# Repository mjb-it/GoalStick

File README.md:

# GoalStick

An NHL goal celebration system that triggers LED light shows when your favorite team scores. The system consists of three components:

- **Raspberry Pi Service** (Python) - Monitors NHL games and detects goals
- **Android App** (Kotlin) - Companion app for configuration via Bluetooth
- **ESP32 Firmware** (Arduino/C++) - Controls WS2812B LED strip animations

## Repository Structure

```
GoalStick/
├── PythonSrc/       # Raspberry Pi Python service
├── Android/         # Android companion app
├── ESP32/           # ESP32 LED controller firmware
├── Makefile         # Build and test automation
└── README.md
```

---

# Raspberry Pi Service (Python)

The core service that monitors NHL games and communicates with the ESP32 to trigger celebrations.

## Requirements

- Raspberry Pi Zero 2 W (or any Pi with GPIO)
- Python 3.9+
- Serial connection to ESP32

## Installation

```bash
cd PythonSrc
pip install -e .
```

Or using Make:
```bash
make python-install
```

## Usage

```bash
cd PythonSrc

# Start the goal monitoring service
python main.py

# Set your team (persists across reboots)
python main.py --team WSH

# Show currently configured team
python main.py --show-team

# Enter Bluetooth pairing mode
python main.py --pair
```

## Testing

```bash
# Run unit tests (69 tests)
make python-test

# Run with coverage report
make python-test-cov
```

## Configuration Options

| Parameter | Type | Default | Description |
|-----------|------|---------|-------------|
| `team_abbr` | str | "WSH" | NHL team abbreviation |
| `check_interval` | float | 2.0 | Seconds between goal checks during live games |
| `daily_check_hour` | int | 8 | Hour (24-hour format) to check daily schedule |
| `pre_game_wake_minutes` | int | 5 | Minutes before game to wake up |
| `serial_port` | str | "/dev/serial0" | Serial port for ESP32 communication |
| `serial_baud_rate` | int | 115200 | Baud rate for serial communication |
| `pairing_button_pin` | int | 17 | BCM GPIO pin for pairing button |
| `esp32_reset_pin` | int | 27 | BCM GPIO pin connected to ESP32 EN |

## Dependencies

- `nhlpy` - NHL API client
- `python-dateutil` - Date parsing utilities
- `pyserial` - Serial communication with ESP32
- `RPi.GPIO` - GPIO control (optional, for button/reset)

---

# Android App (Kotlin)

Companion app for configuring the GoalStick via Bluetooth.

## Requirements

- Android Studio Hedgehog (2023.1.1) or newer
- Android SDK 34
- Java 17 (for command-line builds)

## Features

- Bluetooth device discovery and pairing
- WiFi credential configuration
- NHL team selection (all 32 teams)
- Send configuration to Raspberry Pi

## Building

### Using Android Studio (Recommended)

1. Open `Android/` folder in Android Studio
2. Sync Gradle files
3. Build → Build Bundle(s) / APK(s) → Build APK(s)

### Using Command Line

```bash
# Requires Android SDK and Java 17
make android-build

# APK location:
# Android/app/build/outputs/apk/debug/app-debug.apk
```

### Installing on Device

```bash
# With device connected via USB
make android-install

# Or manually:
adb install Android/app/build/outputs/apk/debug/app-debug.apk
```

## Project Structure

```
Android/
├── app/src/main/
│   ├── java/com/goalstick/android/
│   │   ├── MainActivity.kt           # Main UI
│   │   ├── bluetooth/BluetoothManager.kt  # BT connection
│   │   ├── data/ConfigurationData.kt # Team data
│   │   └── ui/                        # UI components
│   ├── res/layout/                    # XML layouts
│   └── AndroidManifest.xml
├── build.gradle
└── settings.gradle
```

---

# ESP32 Firmware (Arduino)

Controls the WS2812B LED strip and receives commands from the Raspberry Pi.

## Requirements

- ESP32 development board
- Arduino IDE or PlatformIO
- FastLED library

## Building

1. Open `ESP32/hockey_stick_light_controller.ino` in Arduino IDE
2. Install FastLED library (Sketch → Include Library → Manage Libraries)
3. Select board: ESP32 Dev Module
4. Upload to ESP32

## Pin Configuration

| Pin | Function |
|-----|----------|
| GPIO 4 | LED Data Out |
| GPIO 16 (RX2) | Serial RX from Raspberry Pi |
| GPIO 17 (TX2) | Serial TX to Raspberry Pi |

## Serial Protocol

The ESP32 listens on Serial2 at 115200 baud:

| Command | Format | Description |
|---------|--------|-------------|
| Celebrate | `C:RRGGBB,RRGGBB,...\n` | Trigger goal animation with hex colors |
| Idle | `I\n` | Stop animation and clear strip |
| Ping | `P\n` | Health check, responds with `PONG\n` |

Example: `C:FFFFFF,002D62,E51937\n` (Washington Capitals colors)

---

# Hardware Setup

## Components

- **Raspberry Pi Zero 2 W** - Runs the Python service
- **ESP32** - Controls LED strip via serial
- **WS2812B LED Strip** - 300+ addressable LEDs
- **5V Power Supply** - Minimum 2A (more for full strip)
- **Momentary Push Button** - For Bluetooth pairing

## Wiring Diagram

### Raspberry Pi ↔ ESP32

| Raspberry Pi | ESP32 | Purpose |
|--------------|-------|---------|
| GPIO 14 (TX) | GPIO 16 (RX2) | Serial data |
| GPIO 27 | EN | ESP32 reset (optional) |
| GND | GND | Common ground |

### ESP32 ↔ LED Strip

| ESP32 | LED Strip | Purpose |
|-------|-----------|---------|
| GPIO 4 | Data In (via 470Ω resistor) | LED control |
| VIN | 5V | Power |
| GND | GND | Ground |

### Pairing Button

| Raspberry Pi | Button |
|--------------|--------|
| GPIO 17 | Pin 1 (uses internal pull-up) |
| GND | Pin 2 |

Press and hold for 3 seconds to enter pairing mode.

## Hardware Protection

- **1000µF Capacitor** - Across 5V/GND rails near power input
- **470Ω Resistor** - Between ESP32 GPIO 4 and LED Data In
- **Logic Level Shifter** (optional) - 74AHCT125 for long cable runs

---

# Build & Deployment

For hands-free installation and automated deployment instructions, see **[DEPLOYMENT.md](DEPLOYMENT.md)**.

Quick build commands:

```bash
make help          # Show all available targets
make all           # Build everything
make test          # Run all tests
make clean         # Clean all artifacts
```

---

# NHL Team Abbreviations

| Conference | Teams |
|------------|-------|
| Eastern | BOS, BUF, CAR, CBJ, DET, FLA, MTL, NJD, NYI, NYR, OTT, PHI, PIT, TBL, TOR, WSH |
| Western | ANA, ARI, CGY, CHI, COL, DAL, EDM, LAK, MIN, NSH, SEA, SJS, STL, VAN, VGK, WPG |

---

# License

This project is licensed under the MIT License - see the [LICENSE](LICENSE) file for details.

# Contributing

1. Fork the repository
2. Create a feature branch
3. Make your changes
4. Add tests if applicable
5. Submit a pull request

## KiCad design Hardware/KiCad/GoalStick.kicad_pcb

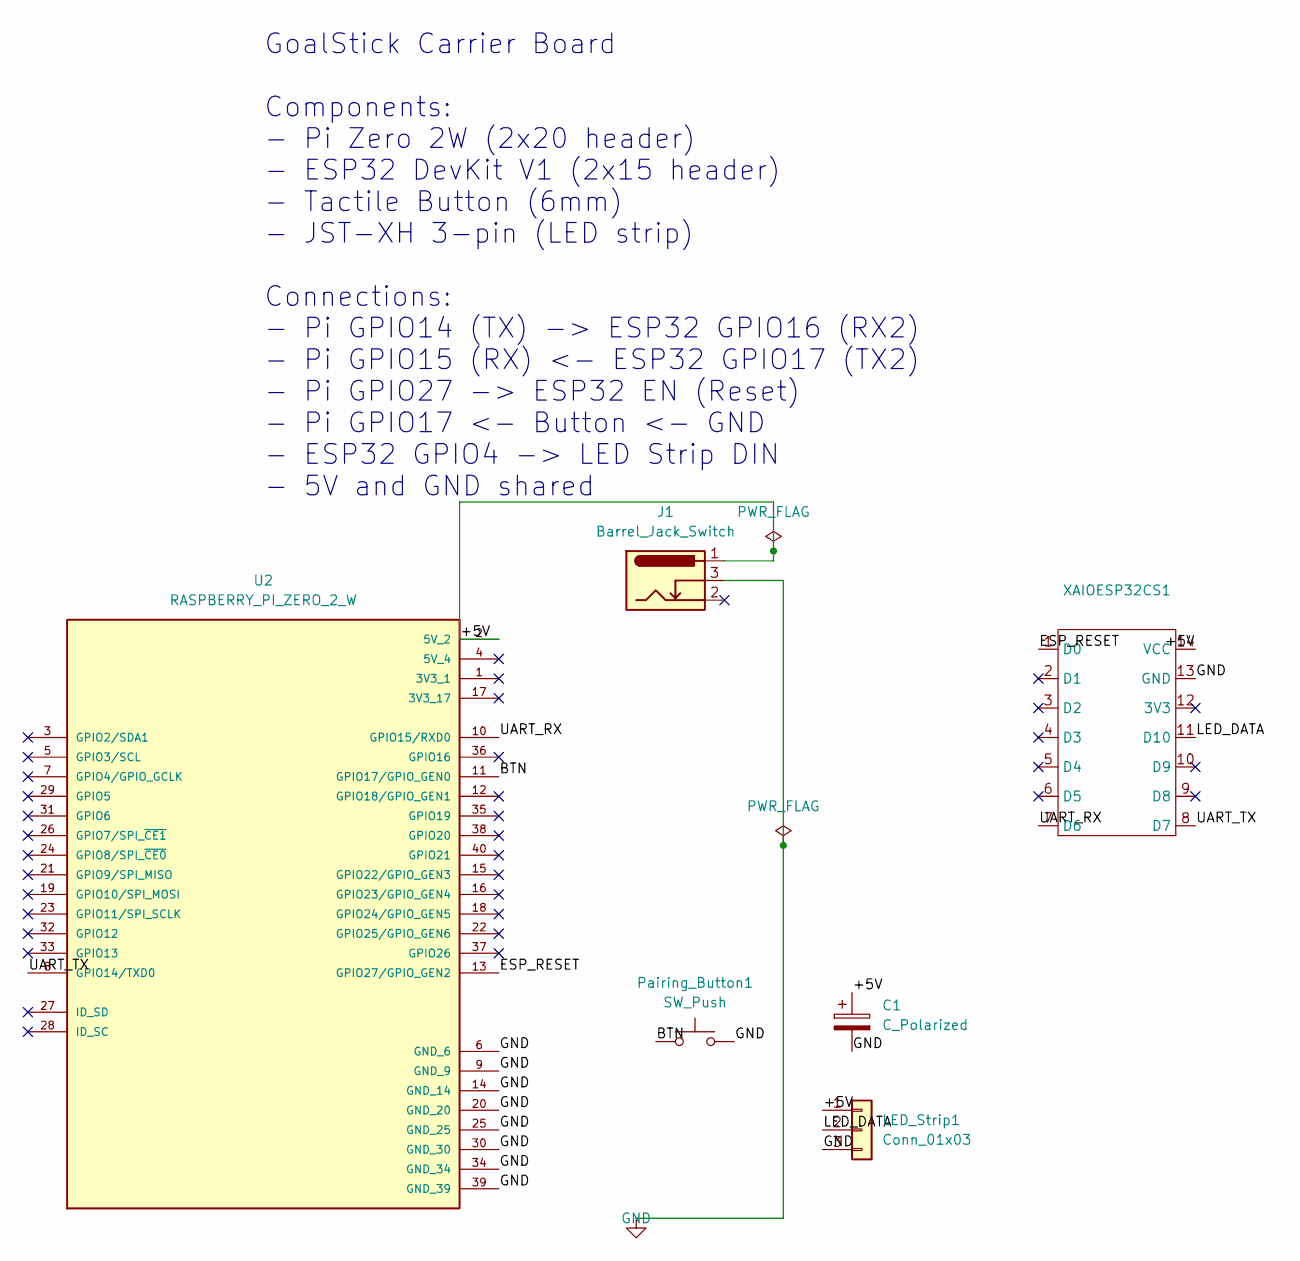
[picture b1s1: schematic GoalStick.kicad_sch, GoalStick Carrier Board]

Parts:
C1: C_Polarized; CP_Radial_D8.0mm_P3.50mm
J1: Barrel_Jack_Switch; BarrelJack_Horizontal
LED_Strip1: Conn_01x03; JST_XH_B3B-XH-A_1x03_P2.50mm_Vertical
Pairing_Button1: SW_Push; SW_PUSH_6mm
U2: RASPBERRY_PI_ZERO_2_W; MODULE_RASPBERRY_PI_ZERO_2_W; PARTREV April 2024
XAIOESP32CS1: XIAO-ESP32-C3-DIP

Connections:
/+5V: C1.1, J1.1, LED_Strip1.1, U2.2 (5V_2), XAIOESP32CS1.14 (VCC)
/BTN: Pairing_Button1.1, U2.11 (GPIO17/GPIO_GEN0)
/ESP_RESET: U2.13 (GPIO27/GPIO_GEN2), XAIOESP32CS1.1 (D0)
/LED_DATA: LED_Strip1.2, XAIOESP32CS1.11 (D10)
/UART_RX: U2.10 (GPIO15/RXD0), XAIOESP32CS1.7 (D6)
/UART_TX: U2.8 (GPIO14/TXD0), XAIOESP32CS1.8 (D7)
GND: C1.2, J1.3, LED_Strip1.3, Pairing_Button1.2, U2.6 (GND_6), U2.9 (GND_9), U2.14 (GND_14), U2.20 (GND_20), U2.25 (GND_25), U2.30 (GND_30), U2.34 (GND_34), U2.39 (GND_39), XAIOESP32CS1.13 (GND)

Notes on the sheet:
GoalStick Carrier Board Components: - Pi Zero 2W (2x20 header) - ESP32 DevKit V1 (2x15 header) - Tactile Button (6mm) - JST-XH 3-pin (LED strip) Connections: - Pi GPIO14 (TX) -> ESP32 GPIO16 (RX2) - Pi GPIO15 (RX) <- ESP32 GPIO17 (TX2) - Pi GPIO27 -> ESP32 EN (Reset) - Pi GPIO17 <- Button <- GND - 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

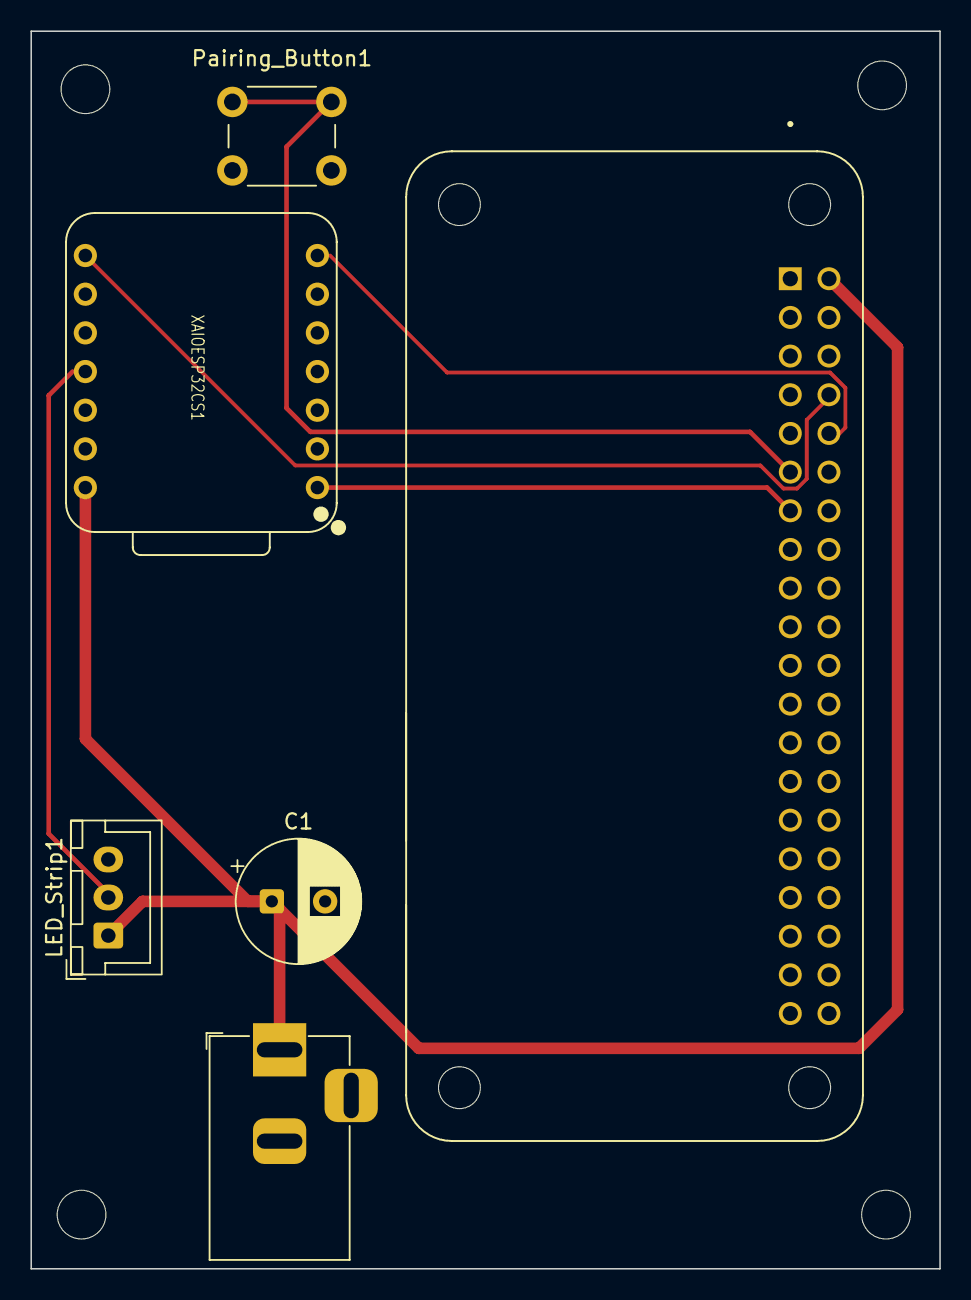
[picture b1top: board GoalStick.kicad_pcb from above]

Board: 2 copper layers, 59.7 x 81.3 mm, 7 parts (0 on the bottom side), 7 nets.

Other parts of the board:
Mount: MountingHole_3.2mm_M3

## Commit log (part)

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2026-01-14 First working pass - gets daily game schedules for a given team.
2026-01-28 Add automated scheduler for NHL goal monitoring
    - Implement StickCheckScheduler with daily execution during hockey season
    - Add smart sleep management (wakes before game start)
    - Add 0.5 second interval checking during live games
    - Improve scorekeeper API efficiency and error handling
    - Add retry logic with exponential backoff
    - Add comprehensive configuration options
2026-01-31 Fix ESP32 pin assignments for Serial2 and LED data
    - Update ESP32 firmware to use Serial2 on GPIO 16 (RX) for Pi communication
    - Move LED data pin from GPIO 16 to GPIO 4 to avoid conflict
    - Add debug logging for received commands
    - Update ESP32.md and README.md with correct wiring diagrams
2026-01-31 Add unit test suite with pytest
    - Add tests directory with pytest configuration
    - Add 69 unit tests covering:
    - ConfigStore: persistence, save/load, team management
    - LEDController: serial communication, ping, celebrate, idle
    - HockeySeasonDetector: all months and edge cases
    - ESP32Reset: GPIO setup, reset, cleanup
2026-02-01 Reorganize repo: move Python code to PythonSrc directory
    - Move StickCheck package, main.py, tests, pyproject.toml,
    pytest.ini, and team_colors.json to PythonSrc/
    - Update pyproject.toml readme path to ../README.md
    - Update README installation instructions to cd PythonSrc first
    - All 69 tests pass after reorganization
2026-02-01 Add Android app Bluetooth configuration and Pi-side server
    Android App:
    - Add Bluetooth permissions to manifest
    - Create BluetoothManager for device discovery and connection
    - Create MainActivity with scan, connect, and configuration UI
    - Add WiFi SSID/password input fields
    - Add NHL team selection spinner with all 32 teams
2026-02-01 Add Makefile for building and testing
    Android targets:
    - android-build: Build debug APK
    - android-release: Build release APK
    - android-install: Install APK to device
    - android-clean: Clean build artifacts
    Python targets:
2026-02-01 Fix Android build: update Gradle 8.10.2, AGP 8.5.0, use Java 17
    - Update Gradle wrapper to 8.10.2 for better Java compatibility
    - Update Android Gradle Plugin to 8.5.0
    - Update Kotlin to 1.9.24
    - Update Makefile to use Java 17 (JAVA_HOME) for Android builds
    - Requires Android SDK to be installed for builds to complete
2026-02-01 Fix Android build: add AndroidX, launcher icons
    - Add android.useAndroidX=true to gradle.properties
    - Add adaptive launcher icons (ic_launcher, ic_launcher_round)
    - Add ic_launcher_background and ic_launcher_foreground drawables
    - Build now succeeds: app-debug.apk (5.8MB)
2026-02-01 Add Test Goal button to Android app
    Android:
    - Add 'Test Goal Celebration' button (red, enabled when connected)
    - Add sendTestGoal() in BluetoothManager, MainViewModel, MainActivity
    - Sends {type: 'test_goal'} JSON to Pi
    Python (Pi-side):
    - Update BluetoothServer to handle test_goal messages
2026-02-01 Fix pyproject.toml readme path for editable install
    - Change readme from '../README.md' to 'README.md'
    - Add PythonSrc/README.md with brief package docs
    - Fixes 'Cannot access file outside project' error on pip install
2026-02-01 Fix Bluetooth server socket binding error
    - Add _get_local_bluetooth_address() to get adapter MAC address
    - Use hciconfig or bluetoothctl to find local BT address
    - Bind socket to explicit address instead of empty string
    - Fixes 'bad bluetooth address' error on Pi
2026-02-01 Fix Bluetooth discoverability with hciconfig piscan
    - Use 'hciconfig hci0 piscan' for reliable discoverability
    - Ensure adapter is up before configuring
    - Verify PSCAN and ISCAN flags are set
    - Log warning if discoverability check fails
2026-02-02 Increase Bluetooth data timeout to 5 minutes
    - Changed from 30 seconds to 300 seconds
    - Allows user time to interact with app after connecting
    - Also reordered agent setup before discoverable/pairable
2026-02-02 Remove dbus/PyGObject from pip deps - use system packages on Pi
2026-02-02 Set Bluetooth device class to Computer instead of headset
2026-02-02 Fix sdptool to use sudo for SPP service registration
2026-02-02 Auto-connect to GoalStick if paired, prompt for Bluetooth settings if not
    - Replace device list with auto-connect behavior
    - If GoalStick is paired, automatically connect on app launch
    - If not paired, show button to open Bluetooth settings
    - Re-check on resume when returning from settings
2026-02-02 Add get_config command to load existing configuration
    Pi:
    - Add get_config command handler to Bluetooth server
    - Return current team_abbr from config store
    Android:
    - Add getConfig() method to BluetoothManager
    - Add fetchConfig() to ViewModel with currentConfig StateFlow
2026-02-02 Add WiFi configuration when receiving config from app
    - Create wifi_config.py module with nmcli and wpa_supplicant support
    - Configure WiFi when credentials received via Bluetooth
    - Also save team configuration to config store
2026-02-02 Add rotating file logger with weekly rotation
    - Logs to ~/.goalstick/logs/goalstick.log
    - Rotates weekly on Monday, keeps 4 weeks
    - Also logs to console for journald
2026-02-03 Add periodic status logging during game monitoring (every 60s)
2026-02-03 Reduce logging to every 60s for production
2026-02-03 Add back heartbeat logging every 60 seconds
2026-02-03 Add service targets to Makefile
    - service-install: Install and start systemd service
    - service-uninstall: Remove systemd service
    - service-status: Check service status
2026-02-03 Remove hardcoded paths, use /etc/goalstick for config and /var/log/goalstick for logs
    - Config now stored in /etc/goalstick/config.json
    - Logs now stored in /var/log/goalstick/goalstick.log
    - Service file is now a template with __INSTALL_DIR__ placeholder
    - make service-install creates directories and substitutes paths
    - Added make service-logs to tail the log file
    - Removed old install-service.sh script
2026-02-03 Add make deploy target to install to /opt/goalstick
    - Copies PythonSrc and .git to /opt/goalstick
    - Creates venv with system-site-packages
    - Installs package and systemd service
    - Preserves .git for auto-updates to work
2026-02-03 Make service bulletproof with watchdog and restart policies
    Service file:
    - StartLimitBurst=5 in 300s prevents restart loops
    - WatchdogSec=60 - systemd kills if no ping in 60s
    - MemoryMax=256M, CPUQuota=50% - resource limits
    Scheduler:
    - Background thread pings systemd watchdog every 30s
2026-02-03 Add git safe.directory to deploy target for auto-updates
2026-02-03 Add read-only filesystem support for SD card protection
    - setup-readonly.sh script configures overlayfs
    - Persistent storage for config, WiFi, Bluetooth at /persistent/
    - Logs go to tmpfs (lost on reboot)
    - Auto-updates handle overlay: disable, reboot, update, re-enable, reboot
    - Helper commands: goalstick-status, goalstick-rw, goalstick-ro
    - make deploy-readonly target
2026-02-03 Simplify status LED - off during normal operation
    LED only lights up for special states:
    - Yellow: Booting
    - Blue blink: Pairing mode
    - Cyan blink: Updating
    - Red: Error
    - Red blink: No network
2026-02-05 Fix ESP32 wiring documentation - correct Serial2 pins
    - ESP32 uses GPIO 16 (RX2) and GPIO 17 (TX2) for Serial2
    - Added LED strip wiring section (GPIO 4 for data)
2026-02-05 Fix factory reset and Android app connection handling
    Bug 1: Factory reset now clears Bluetooth cache directory directly
    - Removes paired device directories from /var/lib/bluetooth
    - Restarts Bluetooth service after clearing
    Bug 2: Android app handles connection failure gracefully
    - Shows helpful message when GoalStick is paired but not in config mode
    - Prompts user to press button for 3 seconds to enter pairing mode
2026-02-05 Use LED strip for status indication instead of separate RGB LED
    - StatusLED now sends colors to LED strip via LED controller
    - Removed GPIO pin configuration for separate RGB LED
    - Fixed Capitals team color (CF0A2C instead of E51937) - pure red without green
    - Updated README to reflect LED strip status indicator
    - Updated tests for new Capitals color
2026-02-05 Fix status LED spamming idle commands when in OFF state
    When state is OFF, don't send any commands to LED strip - just sleep.
    This allows celebrations and other LED commands to work properly.
2026-02-05 Fix suspend function call in DeviceAdapter click handler
2026-02-05 Add git safe.directory config for /opt/goalstick
    Fixes warning when service runs git operations as root
2026-02-06 Add PCB design documentation for carrier board
2026-02-06 Add KiCad PCB design for GoalStick carrier board
2026-02-23 Update DEPLOYMENT.md with complete Makefile targets and deployment workflow
2026-02-23 Add dbus-python to rpi dependencies
2026-02-26 Add factory reset safeguards to prevent accidental resets
    - Add 60-second startup delay before factory reset is enabled
    - Require double confirmation (enable, then confirm) for factory reset
    - Check and log initial button state at startup to detect stuck buttons
    - Prevents accidental resets from floating GPIO pins or stuck buttons during boot
2026-02-28 Use America/New_York timezone for all game time displays
2026-03-02 Update .gitignore and remove generated/local KiCad files from repo
    Fixed bad routes on the Pi to ESP32 serial connections, updated SMD pads on the ESP32 to drilled holes.
2026-03-10 Fix Bluetooth adapter bring-up on Pi Zero W 2
    - Add rfkill unblock bluetooth before hciconfig up
    - Use bluetoothctl power on as additional method
    - Add delays between commands for reliability
2026-03-10 Fix Bluetooth adapter bring-up in background command server
    - Add rfkill unblock bluetooth
    - Add bluetoothctl power on
    - Add delays for reliability on Pi Zero W 2
2026-03-10 Fix ESP32 blocking on USB Serial connection
    Removed 'while (!Serial)' which blocked startup until USB was connected.
    ESP32 now starts immediately and listens on Serial1 (Pi UART) without USB.
2026-03-10 Fix team dropdown text color for dark mode
    - Add custom spinner layouts with theme-aware text colors
    - Use ?attr/colorOnSurface for text that adapts to light/dark mode
    - Add spinner background drawable with proper styling
2026-03-18 Add ESP32 OTA firmware updates via arduino-cli
    - Install arduino-cli and ESP32 core in Makefile deploy target
    - Add check_esp32_changes() to detect .ino file changes
    - Add update_esp32_firmware() to compile and upload via serial
    - Integrate ESP32 updates into scheduler auto-update flow
    - Copy ESP32 source to deploy directory for OTA updates
2026-03-18 Fix Android build - consolidate GoalStickConfig class
    - Remove duplicate GoalStickConfig from BluetoothManager
    - Use single GoalStickConfig from ConfigurationData with ipAddress field
    - Add proper imports in BluetoothManager and MainViewModel
2026-03-18 Fix blink phase to show all LEDs divided by team colors
    - Blink phase now displays all 100 LEDs, not just first 10
    - LEDs divided equally by team color count (33 per color for 3-color teams)
    - Example: Capitals score = 33 red, 33 blue, 33 white LEDs blinking
2026-03-19 Add automatic ESP32 bootloader mode entry for OTA uploads
    - Use Pi GPIO13 to control ESP32 GPIO9 (BOOT pin)
    - Use Pi GPIO27 to control ESP32 EN (RESET pin)
    - Automatic bootloader entry sequence before upload
    - No more manual BOOT button press required
    - Requires jumper wire: Pi GPIO13 -> ESP32 D9
